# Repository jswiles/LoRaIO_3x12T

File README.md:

# LoRa Terminal I/O Board

LoRa (3) 12 Screw Terminal I/O Board

- 24LC32A 4K byte EEPROM 
    - Connected to I2C bus 1, can be used  for device configuration and data logging. 

- Buffered TTL RS-232 I/O   
    - UART1 – Debug port 
    - UART2 – User port 

- LTC4311 I2C Bus Accelerator 
    - Up to 1 meter length connections to I2C bus 2 at 400Khz.

Revision 1 

Revision 1 3D Model

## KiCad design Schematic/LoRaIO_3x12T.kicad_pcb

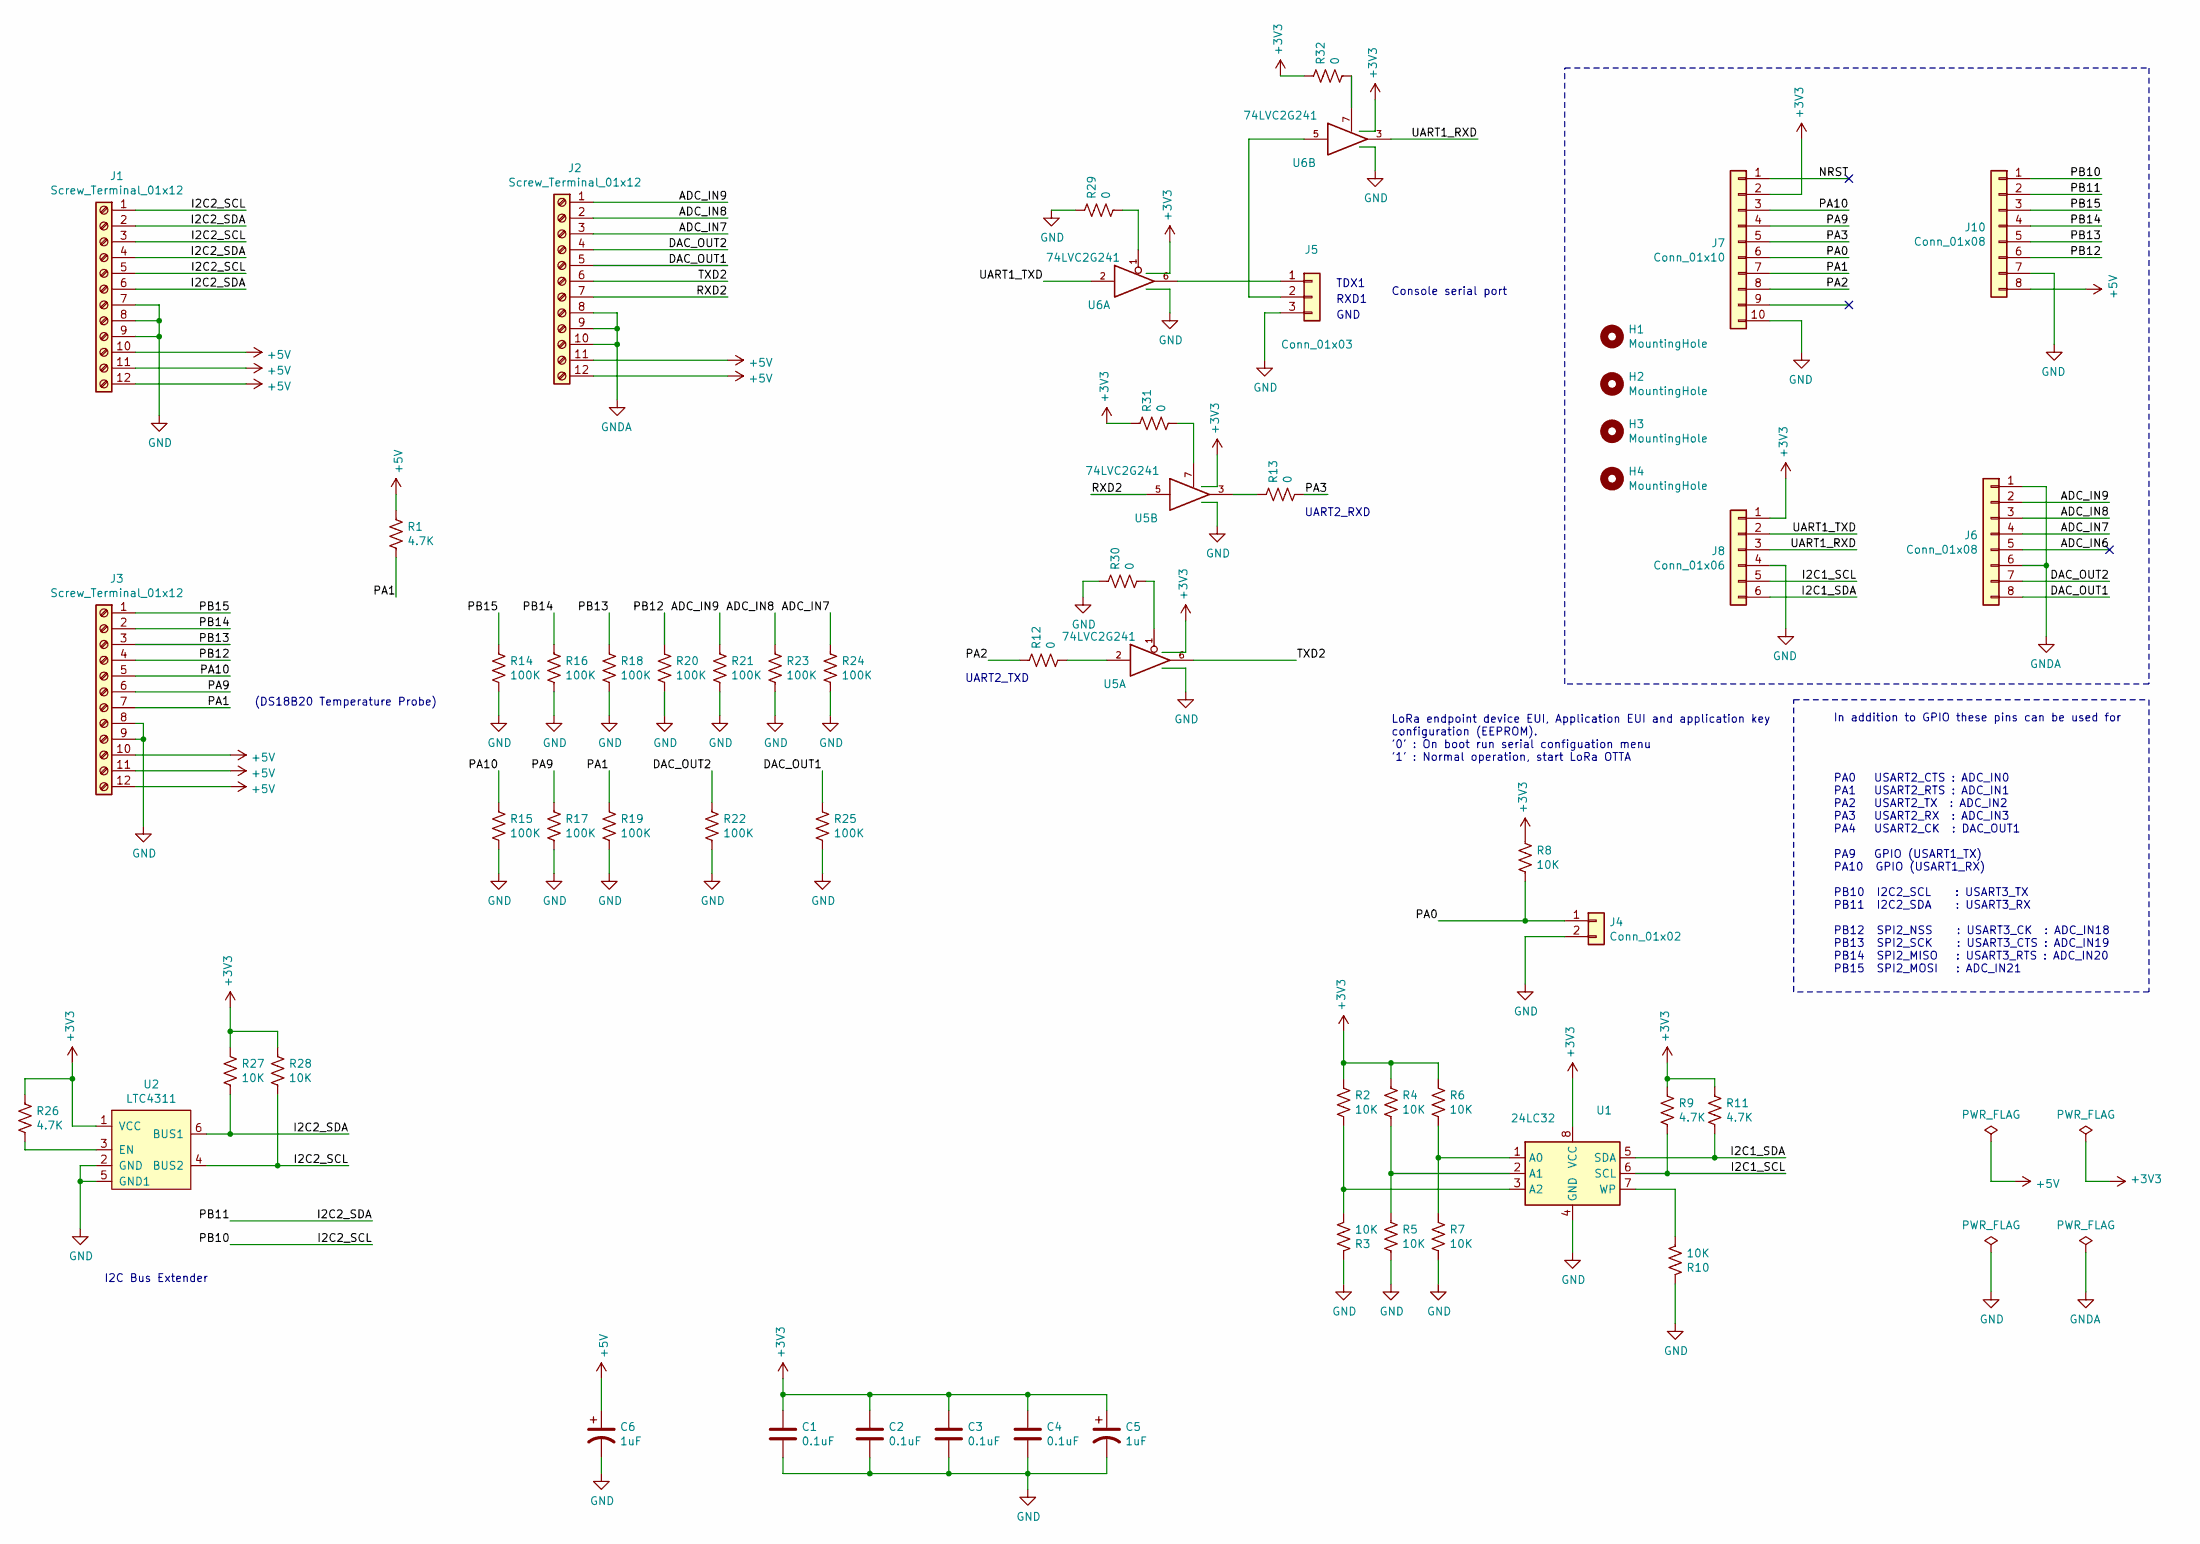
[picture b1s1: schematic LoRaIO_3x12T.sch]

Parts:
C1, C2, C3, C4: 0.1uF; C_0805_2012Metric; DigiKey 311-1140-1-ND
C5, C6: 1uF; CP_EIA-3216-18_Kemet-A_Pad1.58x1.35mm_HandSolder; DigiKey 399-3684-1-ND
H1, H2, H3, H4: MountingHole; MountingHole_2.5mm
J1, J2, J3: Screw_Terminal_01x12; TerminalBlock_TE_1-282834-2_1x12_P2.54mm_Horizontal
J4: Conn_01x02; PinHeader_1x02_P2.54mm_Vertical
J5: Conn_01x03; PinHeader_1x03_P2.54mm_Vertical
J6, J10: Conn_01x08; PinSocket_1x08_P2.54mm_Vertical; DigiKey S1011EC-40-ND
J7: Conn_01x10; PinSocket_1x10_P2.54mm_Vertical; DigiKey S1011EC-40-ND
J8: Conn_01x06; PinSocket_1x06_P2.54mm_Vertical; DigiKey S1011EC-40-ND
R1, R26: 4.7K; R_0805_2012Metric_Pad1.20x1.40mm_HandSolder; DigiKey 311-4.7KARCT-ND
R2, R3, R4, R5, R6, R7, R8, R10, R27, R28: 10K; R_0805_2012Metric_Pad1.20x1.40mm_HandSolder; DigiKey RMCF0805JT10K0CT-ND
R9, R11: 4.7K; R_0805_2012Metric_Pad1.20x1.40mm_HandSolder
R12, R13, R29, R30, R31, R32: 0; R_0805_2012Metric_Pad1.20x1.40mm_HandSolder; DigiKey RMCF0805ZT0R00CT-ND
R14, R15, R16, R17, R18, R19, R20, R21, R22, R23, R24, R25: 100K; R_0805_2012Metric_Pad1.20x1.40mm_HandSolder; DigiKey 311-100KARCT-ND
U1: 24LC32; SO-8_3.9x4.9mm_P1.27mm; DigiKey 24LC32AF-E/SN-ND
U2: LTC4311; sc70_6; DigiKey LTC4311CSC6#TRPBFCT-ND
U5: 74LVC2G241; TSSOP-8_3x3mm_P0.65mm; DigiKey 1727-7019-1-ND
U6: 74LVC2G241; TSSOP-8_3x3mm_P0.65mm

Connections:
+3V3: C1.1, C2.1, C3.1, C4.1, C5.1, J7.2, J8.1, R2.1, R4.1, R6.1, R8.1, R9.1, R11.1, R26.1, R27.1, R28.1, R31.1, R32.1, U1.8 (VCC), U2.1 (VCC), U5.8 (VCC), U6.8 (VCC)
+5V: C6.1, J1.10, J1.11, J1.12, J2.11, J2.12, J3.10, J3.11, J3.12, J10.8, R1.1
/ADC_IN7: J2.3, J6.4, R24.1
/ADC_IN8: J2.2, J6.3, R23.1
/ADC_IN9: J2.1, J6.2, R21.1
/DAC_OUT1: J2.5, J6.8, R25.1
/DAC_OUT2: J2.4, J6.7, R22.1
/I2C1_SCL: J8.5, R9.2, U1.6 (SCL)
/I2C1_SDA: J8.6, R11.2, U1.5 (SDA)
/I2C2_SCL: J1.1, J1.3, J1.5, J10.1, R28.2, U2.4 (BUS2)
/I2C2_SDA: J1.2, J1.4, J1.6, J10.2, R27.2, U2.6 (BUS1)
/PA0: J4.1, J7.6, R8.2
/PA1: J3.7, J7.7, R1.2, R19.1
/PA2: J7.8, R12.1
/PA3: J7.5, R13.2
/PA9: J3.6, J7.4, R17.1
/PA10: J3.5, J7.3, R15.1
/PB12: J3.4, J10.6, R20.1
/PB13: J3.3, J10.5, R18.1
/PB14: J3.2, J10.4, R16.1
/PB15: J3.1, J10.3, R14.1
/RXD2: J2.7, U5.5
/TXD2: J2.6, U5.6
/UART1_RXD: J8.3, U6.3
/UART1_TXD: J8.2, U6.2
GND: C1.2, C2.2, C3.2, C4.2, C5.2, C6.2, J1.7, J1.8, J1.9, J3.8, J3.9, J4.2, J5.3, J7.10, J8.4, J10.7, R3.1, R5.2, R7.2, R10.1, R14.2, R15.2, R16.2, R17.2, R18.2, R19.2, R20.2, R21.2, R22.2, R23.2, R24.2, R25.2, R29.1, R30.1, U1.4 (GND), U2.2 (GND), U2.5 (GND1), U5.4 (GND), U6.4 (GND)
GNDA: J2.8, J2.9, J2.10, J6.1, J6.6
unnamed: J5.1, U6.6
unnamed: J5.2, U6.5
unnamed: R2.2, R3.2, U1.3 (A2)
unnamed: R4.2, R5.1, U1.2 (A1)
unnamed: R6.2, R7.1, U1.1 (A0)
unnamed: R10.2, U1.7 (WP)
unnamed: R12.2, U5.2
unnamed: R13.1, U5.3
unnamed: R26.2, U2.3 (EN)
unnamed: R29.2, U6.1
unnamed: R30.2, U5.1
unnamed: R31.2, U5.7
unnamed: R32.2, U6.7

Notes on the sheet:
In addition to GPIO these pins can be used for
LoRa endpoint device EUI, Application EUI and application key configuration (EEPROM). '0' : On boot run serial configuation menu '1' : Normal operation, start LoRa OTTA
PA0 USART2_CTS : ADC_IN0 PA1 USART2_RTS : ADC_IN1 PA2 USART2_TX : ADC_IN2 PA3 USART2_RX : ADC_IN3 PA4 USART2_CK : DAC_OUT1 PA9 GPIO (USART1_TX) PA10 GPIO (USART1_RX) PB10 I2C2_SCL : USART3_TX PB11 I2C2_SDA : USART3_RX PB12 SPI2_NSS : USART3_CK : ADC_IN18 PB13 SPI2_SCK : USART3_CTS : ADC_IN19 PB14 S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
(DS18B20 Temperature Probe)
TDX1
RXD1
GND
UART2_TXD
UART2_RXD
Console serial port
I2C Bus Extender

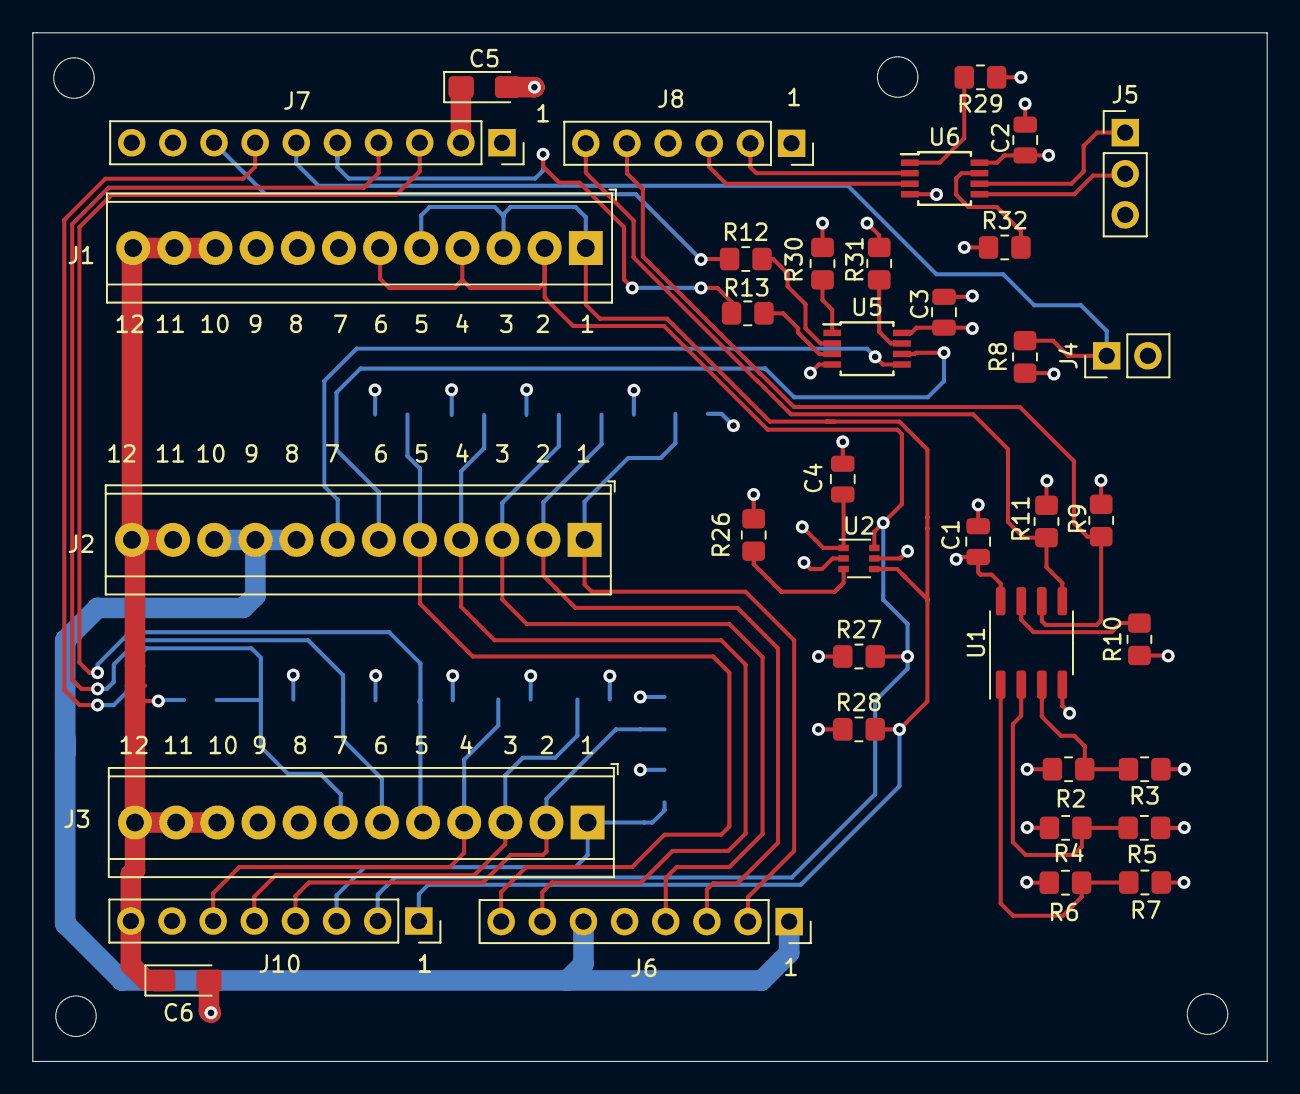
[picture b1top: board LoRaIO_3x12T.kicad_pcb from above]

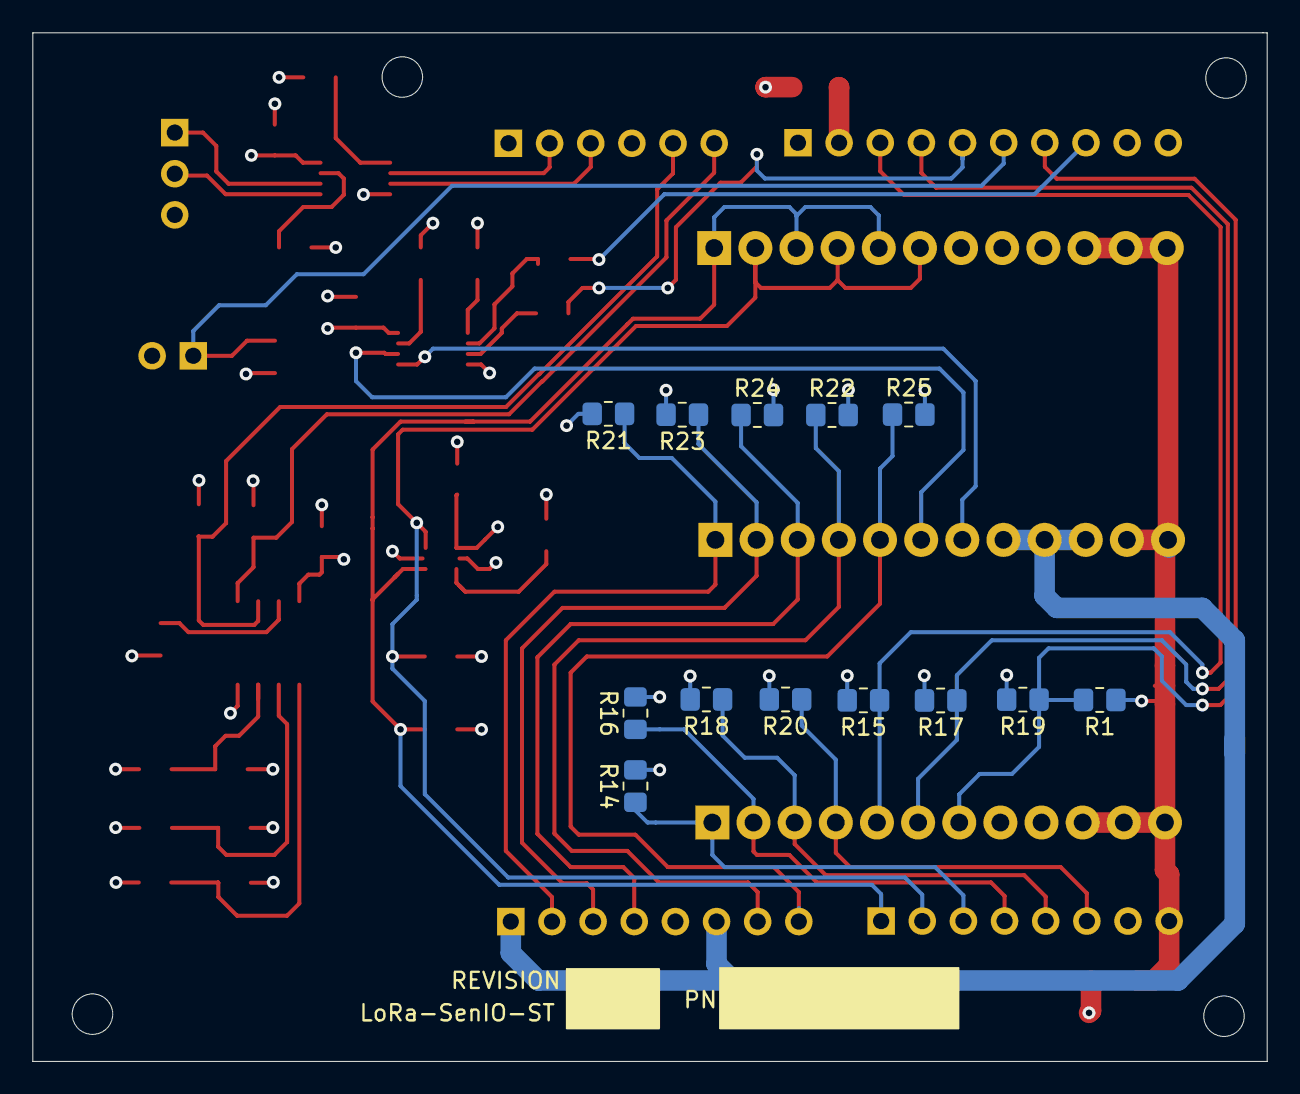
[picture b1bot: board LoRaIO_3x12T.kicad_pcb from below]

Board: 4 copper layers, 76.2 x 63.5 mm, 55 parts (13 on the bottom side), 40 nets.

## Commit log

2022-08-01 Added Photos
2022-08-01 Renamed 3d photo
2022-08-01 Added Documents directory
2022-08-01 Added BOM directory
2022-08-01 Added Schematic directory
